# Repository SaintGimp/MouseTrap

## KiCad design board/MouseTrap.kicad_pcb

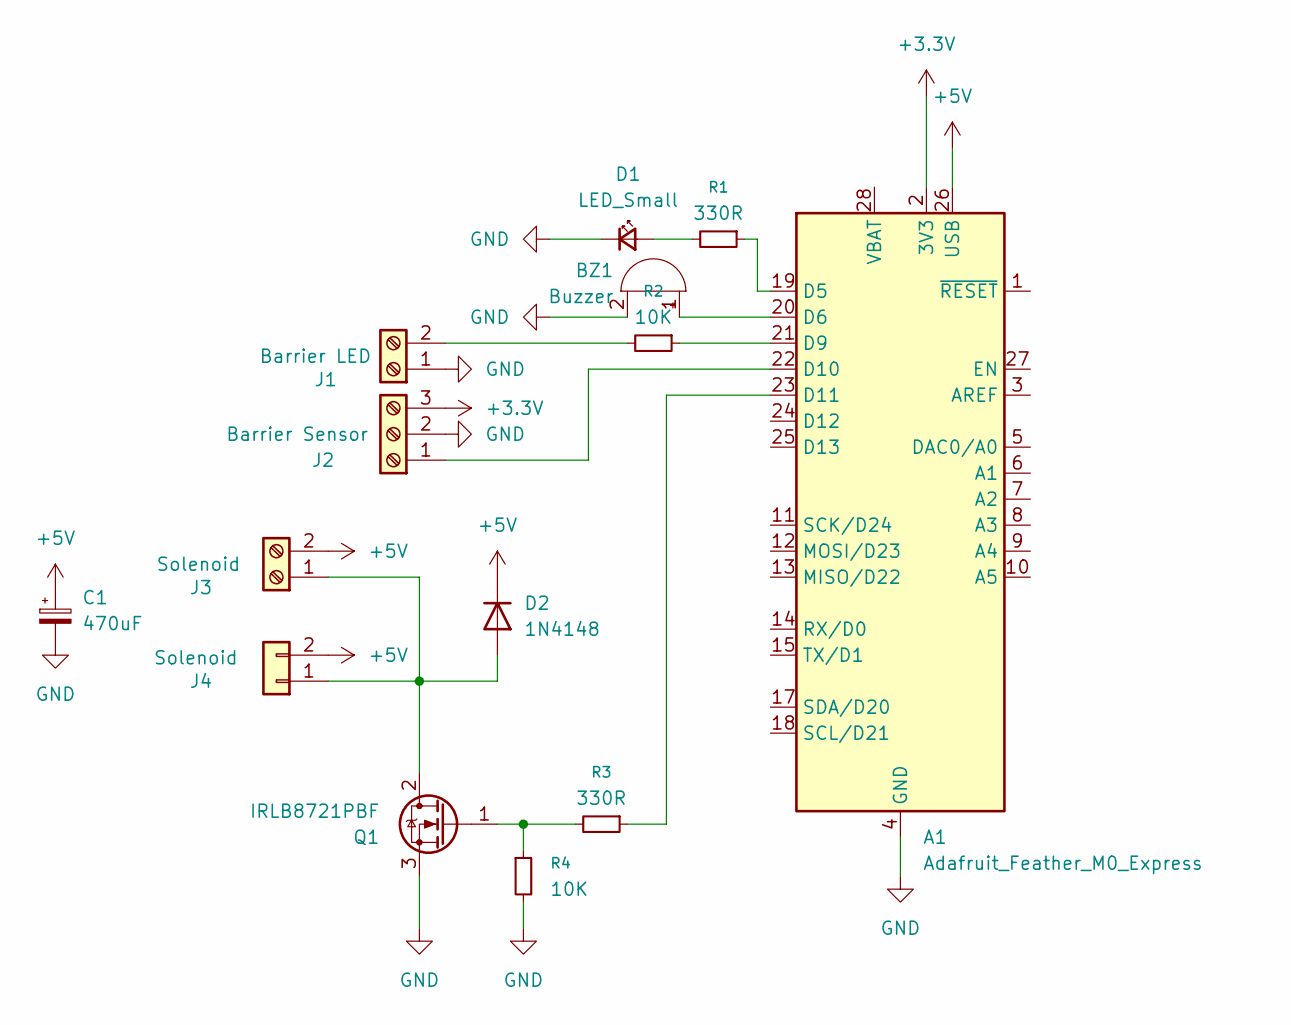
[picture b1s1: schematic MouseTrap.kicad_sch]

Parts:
A1: Adafruit_Feather_M0_Express; Adafruit_Feather
BZ1: Buzzer; Buzzer_12x9.5RM7.6
C1: 470uF; CP_Radial_D6.3mm_P2.50mm
D1: LED_Small; LED_D5.0mm
D2: 1N4148; D_DO-35_SOD27_P7.62mm_Horizontal
J1: Barrier LED; TerminalBlock_TE_282834-2_1x02_P2.54mm_Horizontal
J2: Barrier Sensor; TerminalBlock_TE_282834-3_1x03_P2.54mm_Horizontal
J3: Solenoid; TerminalBlock_TE_282834-2_1x02_P2.54mm_Horizontal
J4: Solenoid; JST_PH_S2B-PH-K_1x02_P2.00mm_Horizontal
Q1: IRLB8721PBF; TO-220-3_Horizontal_TabDown
R1, R3: 330R; R_Axial_DIN0207_L6.3mm_D2.5mm_P7.62mm_Horizontal
R2, R4: 10K; R_Axial_DIN0207_L6.3mm_D2.5mm_P7.62mm_Horizontal

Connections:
+3.3V: A1.2 (3V3), J2.3
+5V: A1.26 (USB), C1.1, D2.1 (K), J3.2, J4.2
GND: A1.4 (GND), A1.16 (GND), BZ1.2 (-), C1.2, D1.1 (K), J1.1, J2.2, Q1.3 (S), R4.2
unnamed: A1.19 (D5), R1.1
unnamed: A1.20 (D6), BZ1.1 (+)
unnamed: A1.21 (D9), R2.1
unnamed: A1.22 (D10), J2.1
unnamed: A1.23 (D11), R3.1
unnamed: D1.2 (A), R1.2
unnamed: D2.2 (A), J3.1, J4.1, Q1.2 (D)
unnamed: J1.2, R2.2
unnamed: Q1.1 (G), R3.2, R4.1

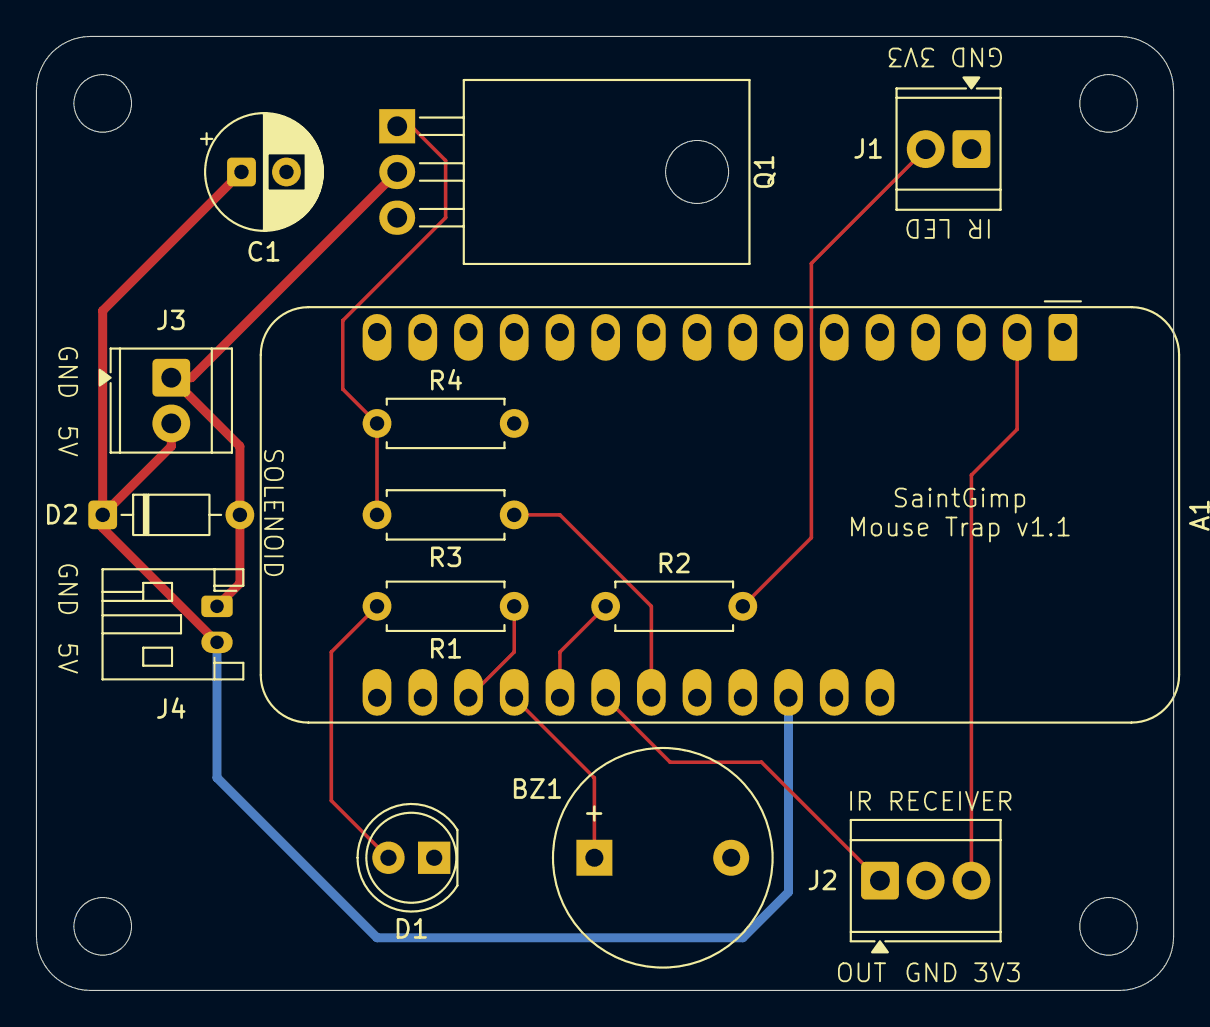
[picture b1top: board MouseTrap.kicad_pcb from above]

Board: 2 copper layers, 63.2 x 53.0 mm, 14 parts (0 on the bottom side), 12 nets.

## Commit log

2022-08-06 Add license
2023-11-07 Add board comments
2024-10-20 Circuit Python version of the mousetrap
2025-03-04 Add neopixel lib
2025-06-28 Add comment
2025-07-29 Update footprints with models
2025-12-06 Board updates
2025-12-06 Code updates
